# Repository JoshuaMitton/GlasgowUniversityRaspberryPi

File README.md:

# GlasgowUniversityRaspberryPi
Raspberry Pi project developing an automatic tea machine using ADC and Qt software

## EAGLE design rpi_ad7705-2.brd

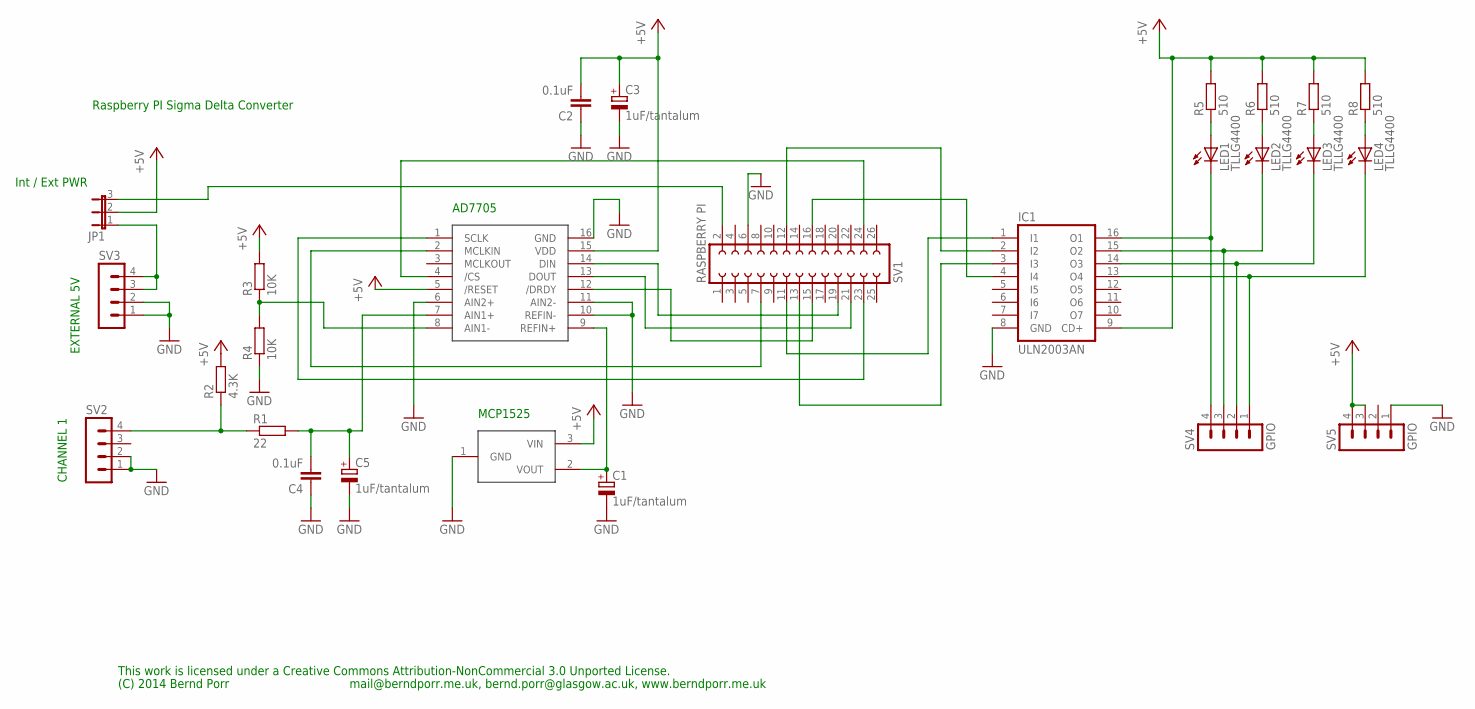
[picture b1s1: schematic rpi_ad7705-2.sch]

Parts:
C1, C3, C5: 1uF/tantalum; TT2D7
C2, C4: 0.1uF; C5B2.5
IC1: ULN2003AN; DIL16
JP1: JP2E; JP2
LED1, LED2, LED3, LED4: TLLG4400; LED3MM
R1: 22; 0207/10
R2: 4.3K; 0207/10
R3, R4: 10K; 0207/10
R5, R6, R7, R8: 510; 0207/10
SV1: RASPBERRY PI; FE13-2
SV2, SV3: MA04-1
SV4, SV5: GPIO; MA04-1
U$1: AD7705; DIP16
U$2: MCP1525; TO92

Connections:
+5V: C2.2, C3.+, IC1.9 (CD+), JP1.2, R2.2, R3.2, R5.2, R6.2, R7.2, R8.2, SV5.3, SV5.4, U$1.5 (/RESET), U$1.15 (VDD), U$2.3 (VIN)
GND: C1.-, C2.1, C3.-, C4.1, C5.-, IC1.8 (GND), R4.1, SV1.6, SV2.1, SV2.2, SV3.1, SV3.2, SV5.1, U$1.6 (AIN2+), U$1.10 (REFIN-), U$1.11 (AIN2-), U$1.16 (GND), U$2.1 (GND)
unnamed: SV1.19, U$1.14 (DIN)
unnamed: SV1.23, U$1.1 (SCLK)
unnamed: SV1.7, U$1.2 (MCLKIN)
unnamed: SV1.24, U$1.4 (/CS)
unnamed: C1.+, U$1.9 (REFIN+), U$2.2 (VOUT)
unnamed: SV1.21, U$1.13 (DOUT)
unnamed: R3.1, R4.2, U$1.8 (AIN1-)
unnamed: C4.2, C5.+, R1.2, U$1.7 (AIN1+)
unnamed: IC1.1 (I1), SV1.11
unnamed: IC1.3 (I3), SV1.13
unnamed: R1.1, R2.1, SV2.4
unnamed: IC1.2 (I2), SV1.12
unnamed: IC1.4 (I4), SV1.16
unnamed: JP1.1, SV3.3, SV3.4
unnamed: LED1.A, R5.1
unnamed: LED2.A, R6.1
unnamed: IC1.16 (O1), LED1.K (C), SV4.4
unnamed: LED3.A, R7.1
unnamed: LED4.A, R8.1
unnamed: IC1.15 (O2), LED2.K (C), SV4.3
unnamed: SV1.15, U$1.12 (/DRDY)
unnamed: JP1.3, SV1.2
unnamed: IC1.14 (O3), LED3.K (C), SV4.2
unnamed: IC1.13 (O4), LED4.K (C), SV4.1

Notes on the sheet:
This work is licensed under a Creative Commons Attribution-NonCommercial 3.0 Unported License.
(C) 2014 Bernd Porr
mail@berndporr.me.uk, bernd.porr@glasgow.ac.uk, www.berndporr.me.uk
AD7705
MCP1525
CHANNEL 1
Raspberry PI Sigma Delta Converter
EXTERNAL 5V
Int / Ext PWR

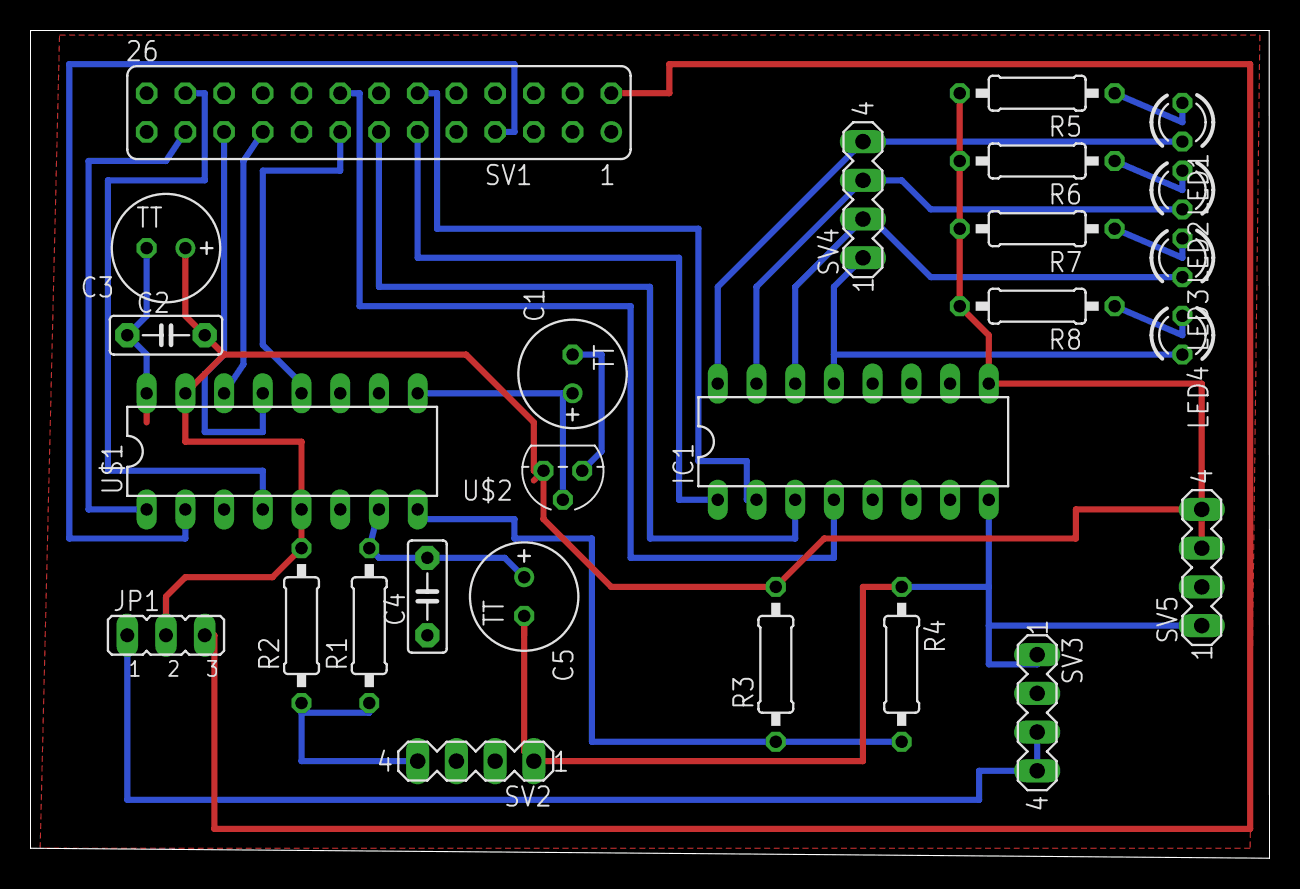
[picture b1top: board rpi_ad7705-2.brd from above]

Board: 2 copper layers, 81.3 x 54.3 mm, 26 parts (0 on the bottom side), 26 nets.

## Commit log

2016-04-14 Added files via upload
    Relay board schematic and, PCB schematic and board file
    Hardware section of Raspberry Pi project
2016-04-15 Files for software
    Software files required for the tea machine.
    To compile:
    qmake
    make
    To run (from terminal):
    sudo startx ./Conprod2
2016-04-15 Delete Relayschematic.sch
    Taken out of software
2016-04-15 Delete rpi_ad7705-2.sch
    Taken out of software
2016-04-15 Delete rpi_ad7705-2.brd
    taken out of software
2016-04-15 Added files via upload
    Update these two files for value changes
2016-04-18 Update common.h
    Added in comments
2016-04-18 Update conproddialog.cpp
    Added comments
2016-04-18 Update conproddialog.h
    added comments
2016-04-18 Update consumer.cpp
    added comments
2016-04-18 Update consumer.h
    commenting.
2016-04-18 Update main.cpp
    comments
2016-04-18 Update myConstants.h
    comment
2016-04-18 Update output_program.cpp
    comments
2016-04-18 Update output_program.h
    comment
2016-04-18 Update producer.cpp
    comment
2016-04-18 Update producer.h
    comment
